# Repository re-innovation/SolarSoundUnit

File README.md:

# SolarSoundUnit
A PIR activated unit which plays random MP3 sounds when triggered. With solar PV charging of LiIon battery

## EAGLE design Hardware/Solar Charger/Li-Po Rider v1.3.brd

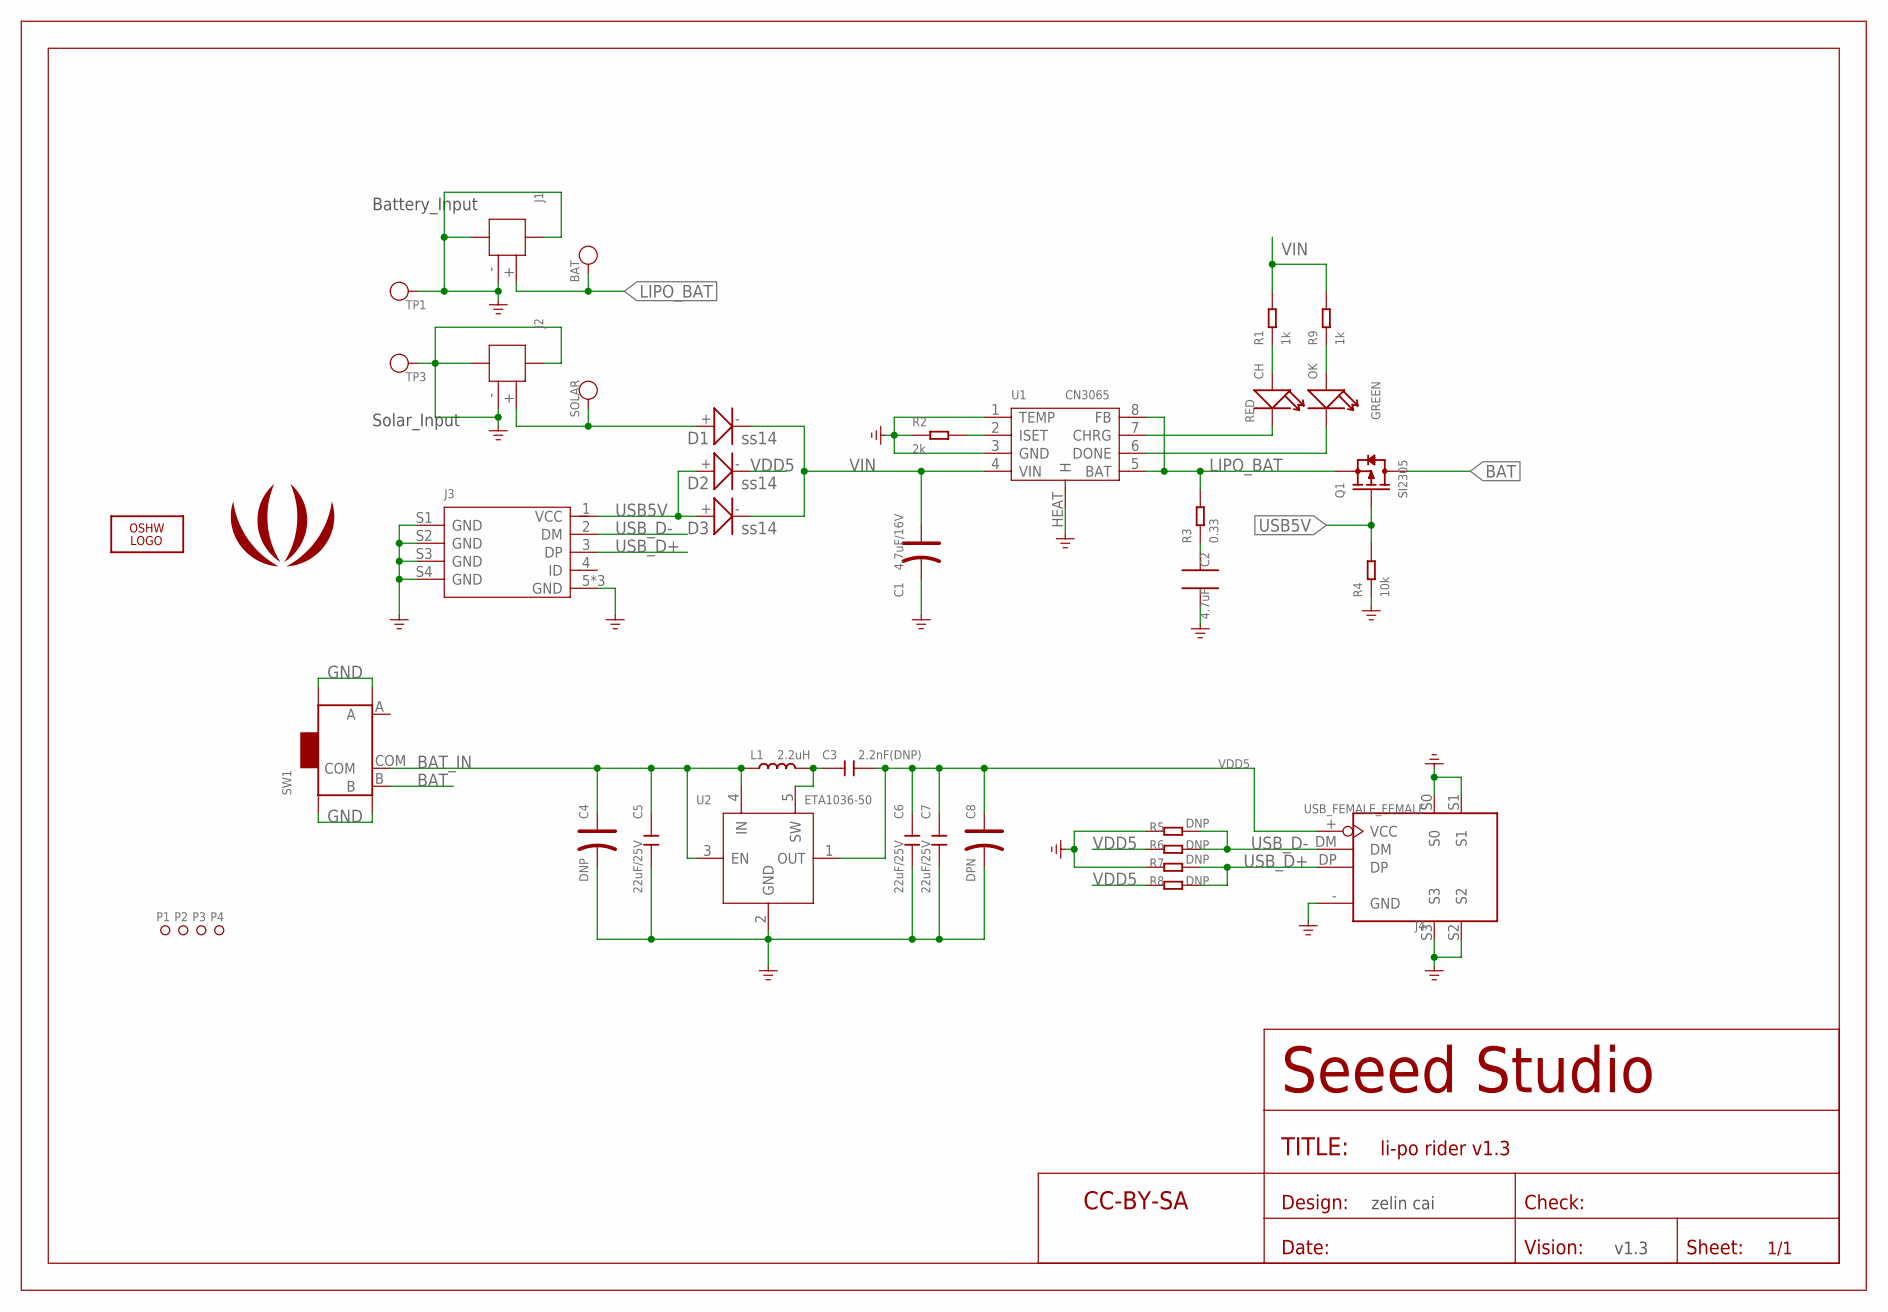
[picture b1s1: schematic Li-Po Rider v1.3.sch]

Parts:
BAT: PAD-TEST-POINT'4545'; TP-D45MIL
C1: 4.7uF/16V; AVX_A
C2: 4.7uF; 0805
C3: 2.2nF(DNP); C0603
C4: DNP; AVX-A
C5, C6, C7: 22uF/25V; C0805
C8: DPN; AVX-A
CH: RED; LED-0603
D1, D2, D3: ss14; D2010
J1, J2: JST-2P-SMD'2.0'; 2P-SMD-2.0-90D
J3: USB-MICRO-5P'5+4P'; 5+4P-SMD-0.65-B
J4: USB_FEMALE_FEMALE; USB_FEMALE_HALF
L1: 2.2uH; L0630
LOGO1: LOGO-OSHW-FILLX0200-NT; OSHW_FILLX200_NOTEXT
OK: GREEN; LED-0603
P1, P2, P3, P4: PAD-MARK'ANNULAR'; ROUND-MARK-1.0
Q1: SI2305; SOT-23
R1, R9: 1k; R0603
R2: 2k; R0603
R3: 0.33; R0603
R4: 10k; R0603
R5, R6, R7, R8: DNP; 0805
SOLAR: PAD-TEST-POINT'4545'; TP-D45MIL
SW1: SWITCH-3+4P; 3+4P-SMD-L6.7*W2.7*H3.2MM
TP1, TP3: PAD-TEST-POINT'4545'; TP-D45MIL
U1: CN3065; DFN-8
U2: ETA1036-50; SOT23-5
U$1: LOGO-SEEEDSTUDIO-SILK; LOGO_SILK
U$2: SEEEDSTUDIO-OPEN-SCH-FRAME; SEEEDSTUDIO-PCB-FRAME

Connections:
BAT: Q1.3 (D), SW1.B
BAT_IN: C4.+, C5.1, L1.1, SW1.COM, U2.3 (EN), U2.4 (IN)
GND: C1.-, C2.2, C4.-, C5.2, C6.2, C7.2, C8.-, J1.3, J1.4, J1.- (2), J2.3, J2.4, J2.- (2), J3.5 (GND), J3.S1 (GND), J3.S2 (GND), J3.S3 (GND), J3.S4 (GND), J3.S5 (GND), J3.S6 (GND), J4.- (GND), J4.S0, J4.S1, J4.S2, J4.S3, R2.1, R4.1, R5.2, R7.2, SW1.SS1, SW1.SS2, SW1.SS3, SW1.SS4, TP1.T, TP3.T, U1.1 (TEMP), U1.3 (GND), U1.HEAT (H), U2.2 (GND)
LIPO_BAT: BAT.T, J1.+ (1), Q1.2 (S), R3.2, U1.5 (BAT), U1.8 (FB)
unnamed: C2.1, R3.1
unnamed: C3.1, L1.2, U2.5 (SW)
unnamed: D1.+, J2.+ (1), SOLAR.T
unnamed: CH.+, R1.1
unnamed: R2.2, U1.2 (ISET)
unnamed: CH.-, U1.7 (CHRG)
unnamed: OK.-, U1.6 (DONE)
unnamed: OK.+, R9.1
USB5V: D2.+, D3.+, J3.1 (VCC), Q1.1 (G), R4.2
USB_D+: J3.3 (DP), J4.DP, R7.1, R8.1
USB_D-: J3.2 (DM), J4.DM, R5.1, R6.1
VDD5: C3.2, C6.1, C7.1, C8.+, D2.-, J4.+ (VCC), R6.2, R8.2, U2.1 (OUT)
VIN: C1.+, D1.-, D3.-, R1.2, R9.2, U1.4 (VIN)

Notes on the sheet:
Solar_Input
Battery_Input
zelin cai
v1.3

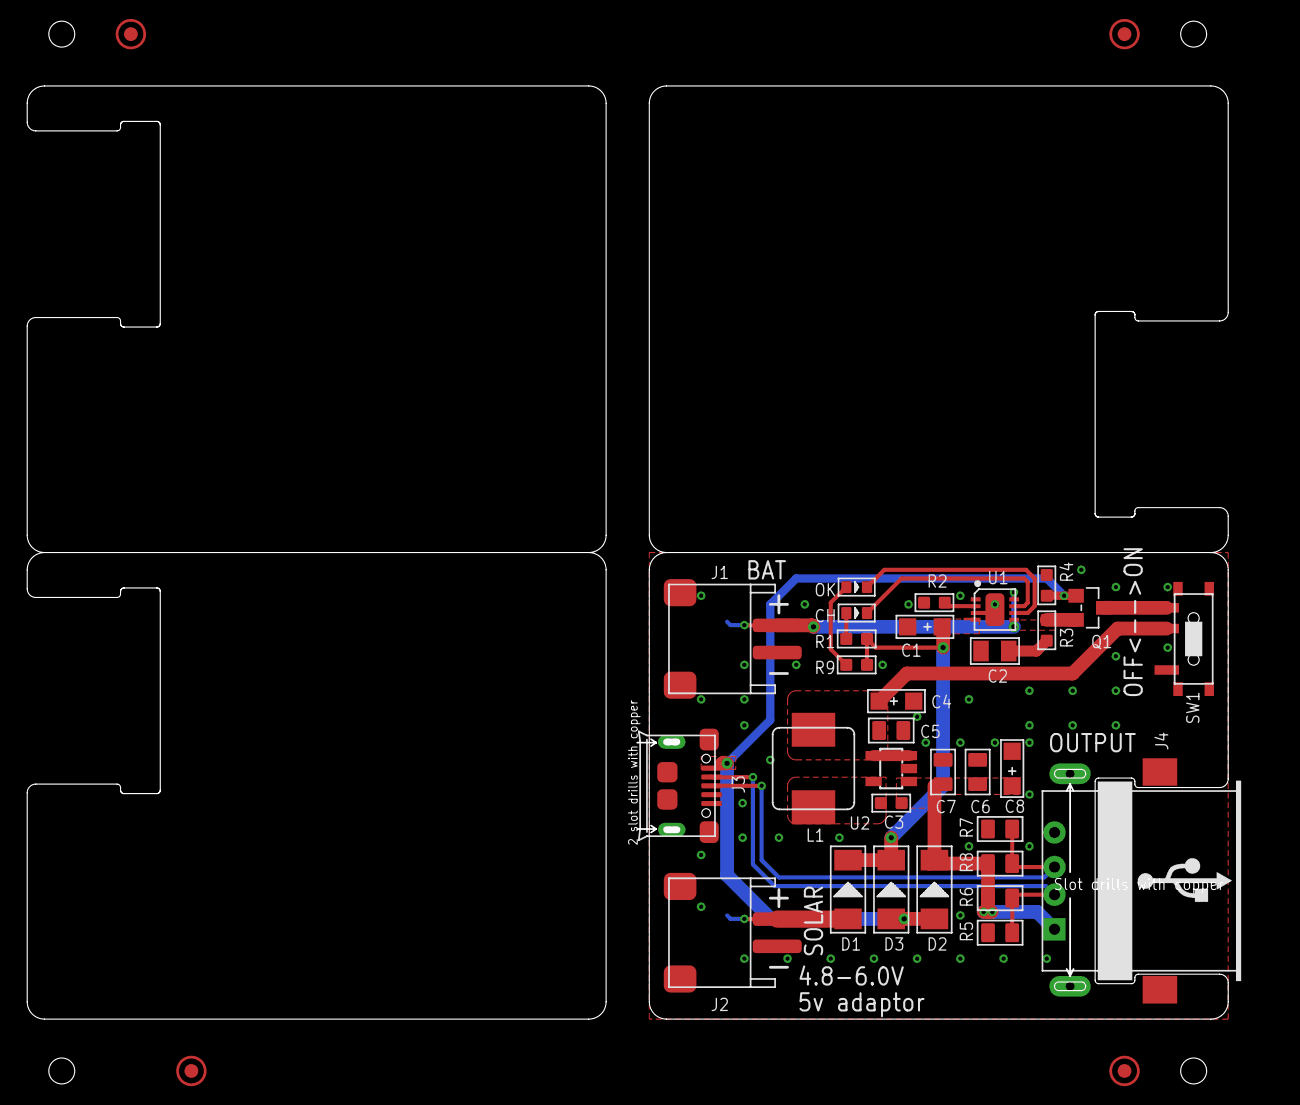
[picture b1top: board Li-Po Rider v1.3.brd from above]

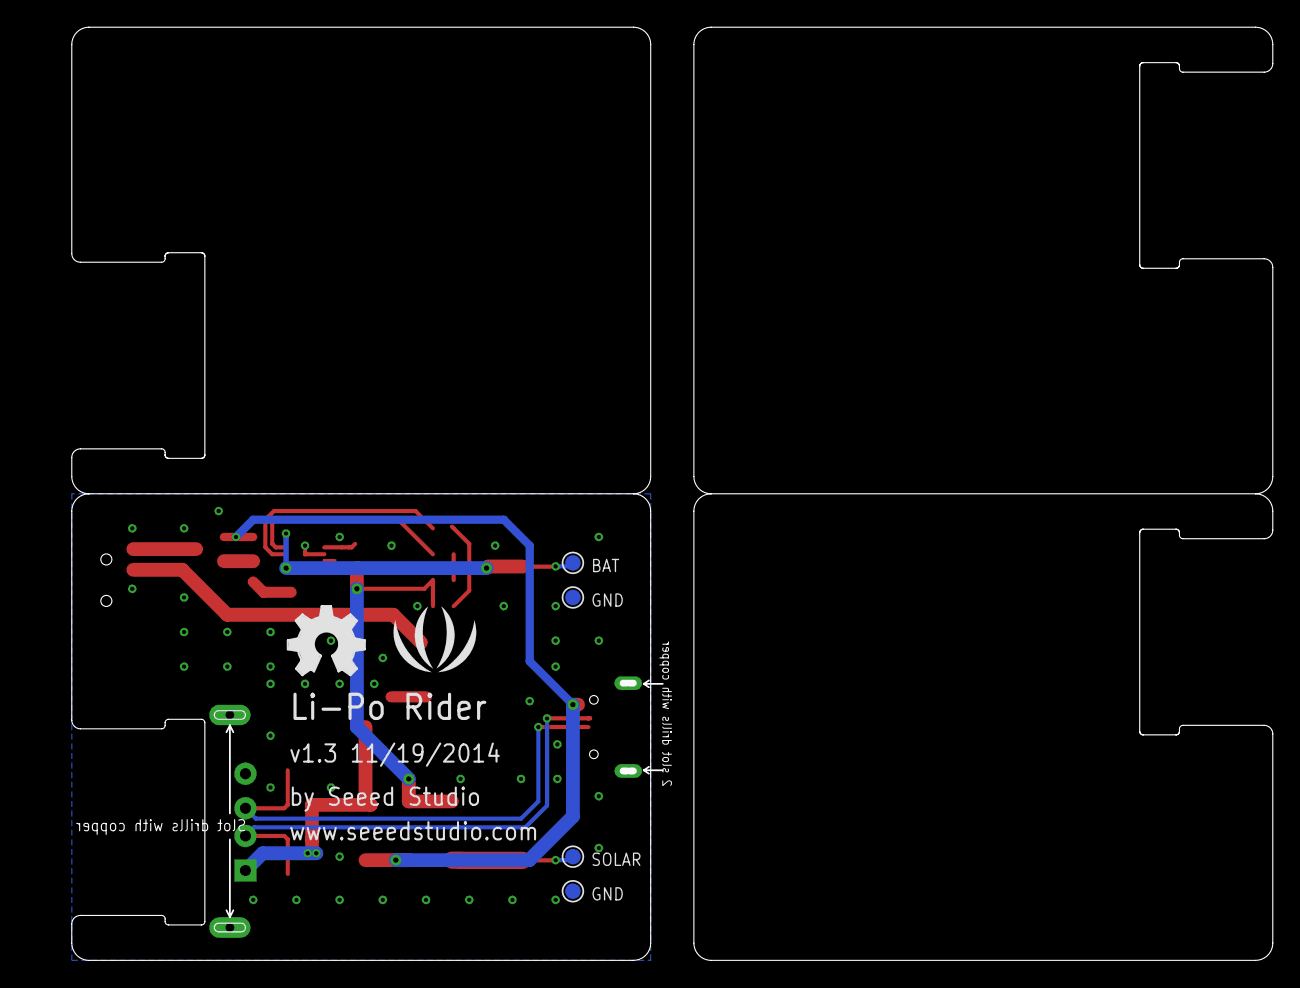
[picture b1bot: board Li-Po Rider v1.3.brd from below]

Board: 2 copper layers, 91.0 x 68.1 mm, 42 parts (6 on the bottom side), 17 nets.

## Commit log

2016-05-27 Added files from previous project
    For keeping up to date in the future

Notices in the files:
parts and their libraries:
moudle-new: This work is licensed under the Creative Commons Attribution 4.0 International License.
To view a copy of this license,visit:
http://creativecommons.org/licenses/by-sa/4.0
moudle-new: CC-BY-SA
